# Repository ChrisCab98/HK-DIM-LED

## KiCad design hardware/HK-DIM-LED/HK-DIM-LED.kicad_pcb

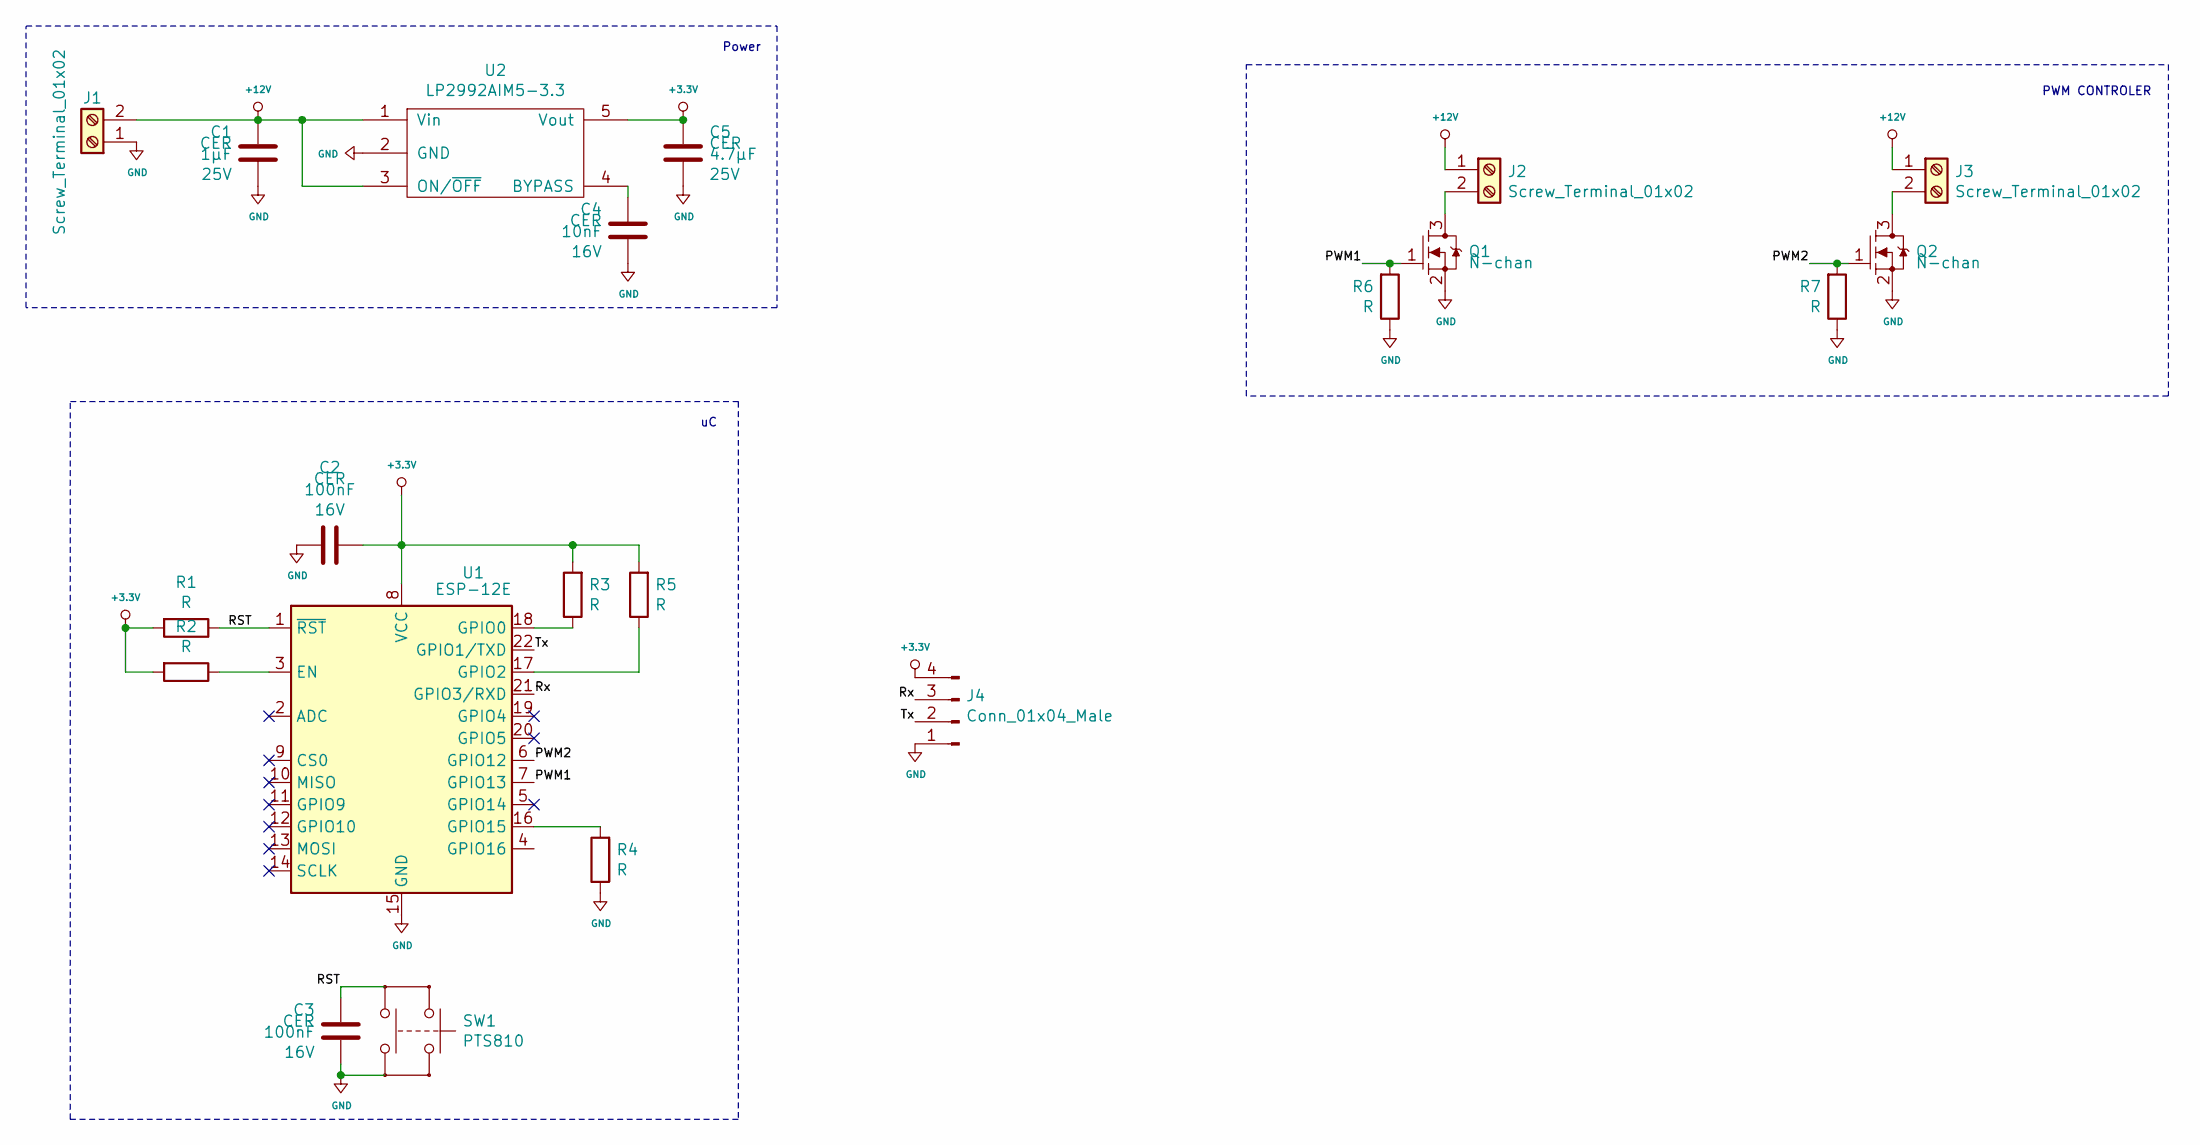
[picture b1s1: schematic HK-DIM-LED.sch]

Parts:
C1: C_0037; C_0603
C2, C3: C_0029; C_0603
C4: C_0017; C_0603
C5: C_0036; C_0603
J1, J2, J3: Screw_Terminal_01x02; TerminalBlock_Phoenix_MKDS-3-2-5.08_1x02_P5.08mm_Horizontal
J4: Conn_01x04_Male; PinHeader_1x04_P2.54mm_Vertical
Q1, Q2: Q_0020; SOT_23
R1, R2, R3, R4, R5, R6, R7: R; R_0603_1608Metric
SW1: SW_0003; PTS810
U1: ESP-12E
U2: U_0005; SOT_23-5

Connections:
+3.3V: C2.2, C5.1, J4.4, R1.2, R2.2, R3.2, R5.2, U1.8 (VCC), U2.5 (Vout)
+12V: C1.2, J1.2, J2.1, J3.1, U2.1 (Vin), U2.3 (ON/~OFF)
/PWM1: Q1.1 (G), R6.2, U1.7 (GPIO13)
/PWM2: Q2.1 (G), R7.2, U1.6 (GPIO12)
/RST: C3.2, R1.1, SW1.3, U1.1 (~RST)
/Rx: J4.3, U1.21 (GPIO3/RXD)
/Tx: J4.2, U1.22 (GPIO1/TXD)
GND: C1.1, C2.1, C3.1, C4.1, C5.2, J1.1, J4.1, Q1.2 (S), Q2.2 (S), R4.1, R6.1, R7.1, SW1.2, U1.15 (GND), U2.2 (GND)
unnamed: C4.2, U2.4 (BYPASS)
unnamed: J2.2, Q1.3 (D)
unnamed: J3.2, Q2.3 (D)
unnamed: R2.1, U1.3 (EN)
unnamed: R3.1, U1.18 (GPIO0)
unnamed: R4.2, U1.16 (GPIO15)
unnamed: R5.1, U1.17 (GPIO2)

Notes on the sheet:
PWM CONTROLER
Power

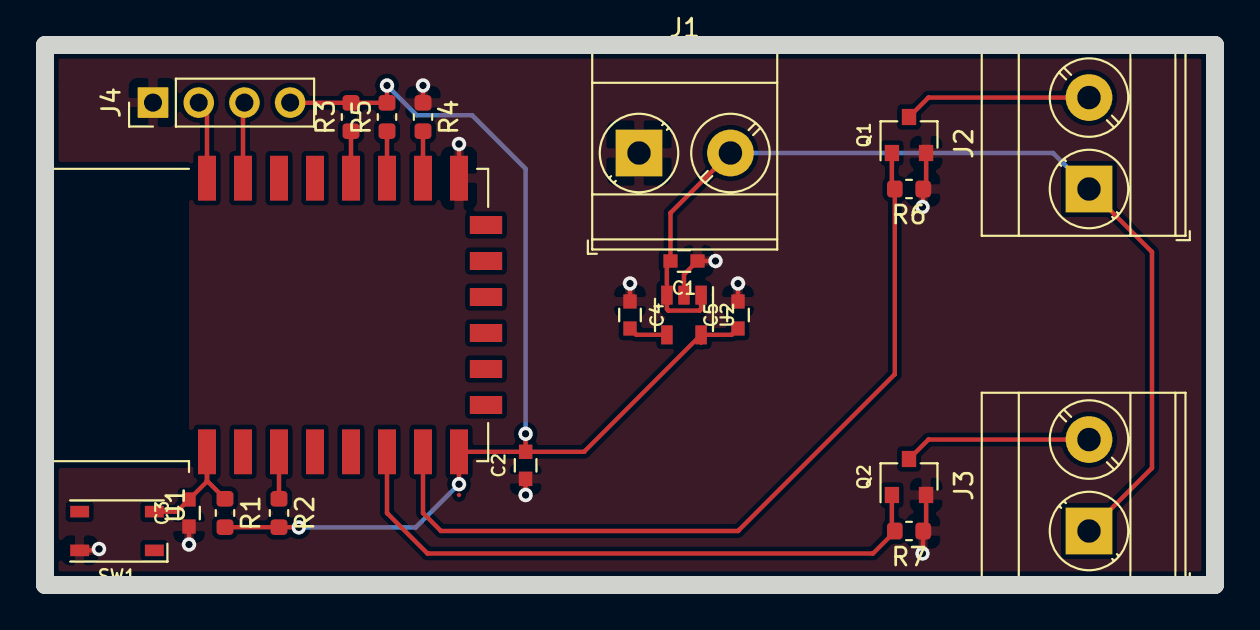
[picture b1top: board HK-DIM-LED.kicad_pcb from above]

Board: 2 copper layers, 65.0 x 30.0 mm, 21 parts (0 on the bottom side), 15 nets.

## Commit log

2020-06-15 create KiCAD Project
